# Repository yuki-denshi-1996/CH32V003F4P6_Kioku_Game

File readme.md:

## 概要
CH32V003F4P6を用いた記憶ゲームです。  
オマケ機能として、1分刻みのタイマー機能も実装してあります。  

## 説明
赤ボタン(PD4)を押すと、ゲームスタートです。  
色と音がなりますので、順番を覚え、ボタンを押してください。  
間違えるとゲームオーバーとなります。  
この時、ハイスコアが更新された場合、ゲームスタート直後の数字のハイスコアが更新されます。  

黄色ボタン(PD7)を押しながら、赤ボタン(PD4)を押すと、ハイスコアがリセットされます。  
(この時、起動直後に7セグメントLEDにCと表示されます)  

黄色ボタン(PD7)を押しながら、青ボタン(PD6)を押すと、難易度の変更ができます。
1(簡単) ~ 9(難しい)まで調整できます。  

緑ボタン(PD5)を押すと、タイマーモードに移行します。  
タイマーモード中に赤ボタン(PD4)を押すことで、リセットされます。  
青ボタン(PD6)と黄色ボタン(PD7)で時間が設定できます。(1分~9分 1分刻み)    
時間を設定した後、緑ボタン(PD5)を押すと、タイマーがスタートします。  
タイマー終了後、緑ボタン(PD5)を押すと、音が停止します。  

## プログラムについて
MounRiver Studio V1.9.1で作成しています。  
User/Kioku_game_program.hに様々な宣言がされています。  
音の周波数などの定数を編集することなどが可能です。  

## 注意点
CH32V003F4P6のNRSTピンをIOピンとして使用してください。  
変更はWCH-LinkUtilityを使うと簡単です。  

## 回路図
回路図はCircuitフォルダにKiCad形式と画像形式で配布しています。  
ご活用ください。  
(基本的に回路図を変更しなければ、配布したプログラムを入れれば動作します)  

部品表は、PDF形式にて配布しています。  
基本的に、秋月電子通商様で手に入る部品を使用しています。

## 問題点について
簡単に自作したプログラムのため、プログラムが汚いです。ご了承ください。  
また、バグ等の問題があった場合、Issuesにお書きください。時間があるときに、修正します。  

## 再配布や使用について
バグ等、修正などができませんので、プログラムソースの再配布はお控えください。  

特にライセンス等を指定していませんが、自由に使用していただいて構いません。  
文化祭等での配布や、キット販売なども構いません。自由にお使いください。  
ただし、プログラムや回路図の使用に関しては、自己責任でお願い致します。  

不明点等有りましたら、下の連絡先までご連絡ください。(できるだけ早く返信します)  

## 連絡先
メールアドレス：matsukawa.software@gmail.com

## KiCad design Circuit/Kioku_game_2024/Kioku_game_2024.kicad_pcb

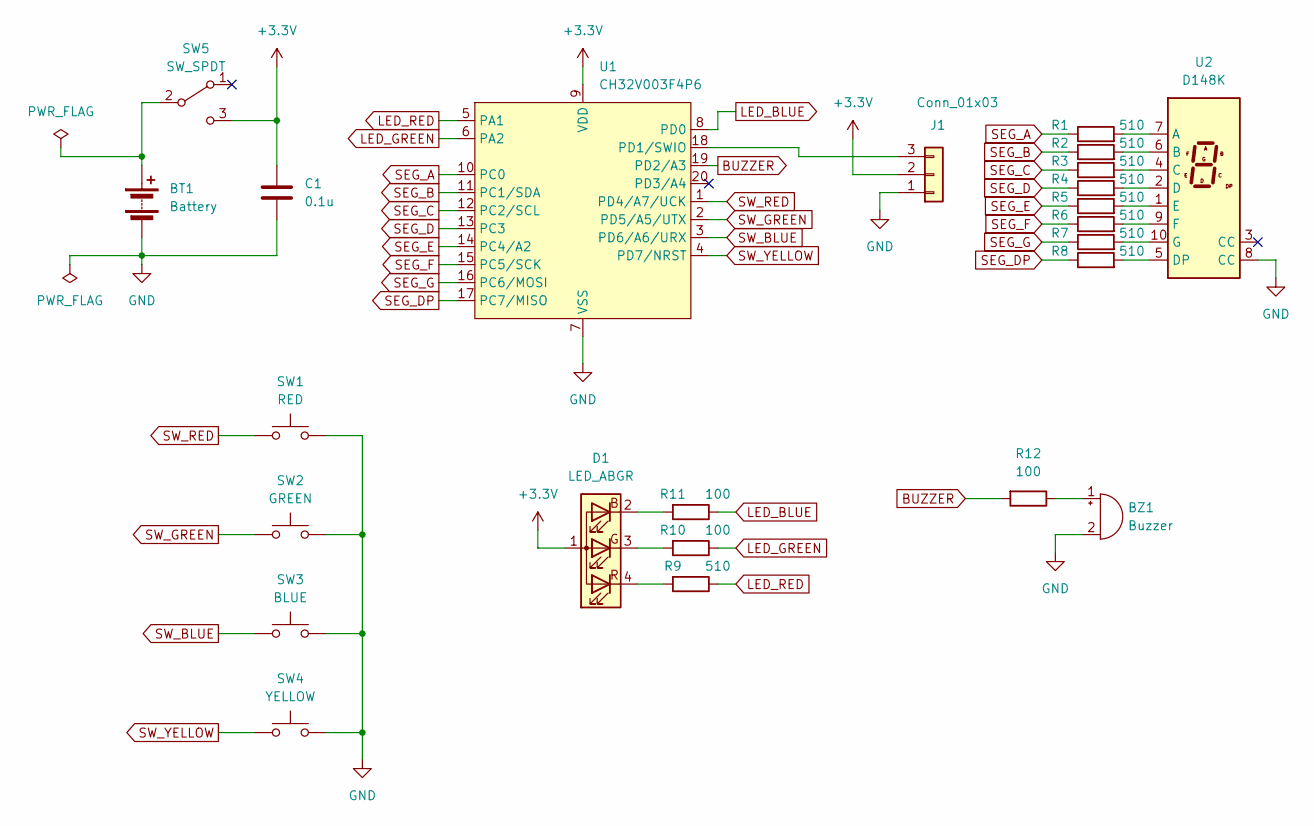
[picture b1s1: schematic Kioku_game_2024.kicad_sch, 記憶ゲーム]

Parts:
BT1: Battery; Coin_Cell_Batt_CR2032
BZ1: Buzzer; AKI_CERAMIC_BUZZER_PKM13EPYH4000-A0
C1: 0.1u; C_DISK_P5.0mm
D1: LED_ABGR; LED_BL-FL7680RGB
J1: Conn_01x03; PinSocket_1x03_P2.54mm_Vertical
R1, R2, R3, R4, R5, R6, R7, R8, R9: 510; R_1_4W
R10, R11, R12: 100; R_1_4W
SW1: RED; SW_PUSH_6mm
SW2: GREEN; SW_PUSH_6mm
SW3: BLUE; SW_PUSH_6mm
SW4: YELLOW; SW_PUSH_6mm
SW5: SW_SPDT; Yuki_PinHeader_1x03_P2.54mm_Vertical
U1: CH32V003F4P6; TSSOP-20_4.4x6.5mm_P0.65mm
U2: D148K; 7SegmentLED_LTS6760_LTS6780

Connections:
+3.3V: C1.1, D1.1 (A), J1.2, SW5.3 (C), U1.9 (VDD)
BUZZER: R12.2, U1.19 (PD2/A3)
GND: BT1.2 (-), BZ1.2 (+), C1.2, J1.1, SW1.2, SW2.2, SW3.2, SW4.2, U1.7 (VSS), U2.8 (CC)
LED_BLUE: R11.1, U1.8 (PD0)
LED_GREEN: R10.1, U1.6 (PA2)
LED_RED: R9.1, U1.5 (PA1)
unnamed: BT1.1 (+), SW5.2 (B)
unnamed: BZ1.1 (-), R12.1
unnamed: D1.2 (BK), R11.2
unnamed: D1.3 (GK), R10.2
unnamed: D1.4 (RK), R9.2
unnamed: J1.3, U1.18 (PD1/SWIO)
unnamed: R1.2, U2.7 (A)
unnamed: R2.2, U2.6 (B)
unnamed: R3.2, U2.4 (C)
unnamed: R4.2, U2.2 (D)
unnamed: R8.2, U2.5 (DP)
unnamed: R5.2, U2.1 (E)
unnamed: R6.2, U2.9 (F)
unnamed: R7.2, U2.10 (G)
SEG_A: R1.1, U1.10 (PC0)
SEG_B: R2.1, U1.11 (PC1/SDA)
SEG_C: R3.1, U1.12 (PC2/SCL)
SEG_D: R4.1, U1.13 (PC3)
SEG_DP: R8.1, U1.17 (PC7/MISO)
SEG_E: R5.1, U1.14 (PC4/A2)
SEG_F: R6.1, U1.15 (PC5/SCK)
SEG_G: R7.1, U1.16 (PC6/MOSI)
SW_BLUE: SW3.1, U1.3 (PD6/A6/URX)
SW_GREEN: SW2.1, U1.2 (PD5/A5/UTX)
SW_RED: SW1.1, U1.1 (PD4/A7/UCK)
SW_YELLOW: SW4.1, U1.4 (PD7/NRST)

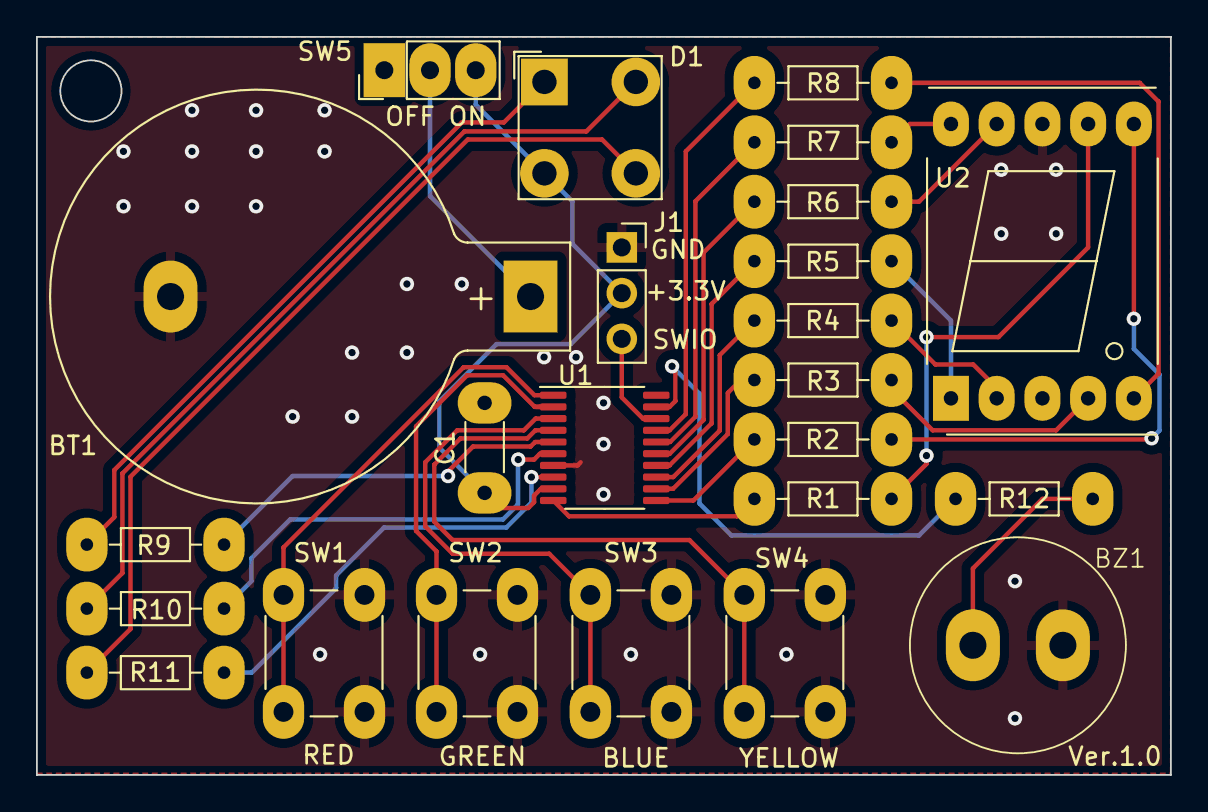
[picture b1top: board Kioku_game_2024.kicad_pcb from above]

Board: 2 copper layers, 63.0 x 41.0 mm, 24 parts (0 on the bottom side), 32 nets.

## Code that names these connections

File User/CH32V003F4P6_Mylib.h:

/*
 * CH32V003F4P6_Mylib.h
 *
 *  Created on: Jan 21, 2024
 *      Author: Yuki(denshi-1996)
 */

#ifndef USER_CH32V003F4P6_MYLIB_H_
#define USER_CH32V003F4P6_MYLIB_H_

//入出力関係_定義
#define MODE_OUTPUT 0b11 //50MHz スピード OUTPUT
#define MODE_OUTPUT_2MHz 0b10
#define MODE_OUTPUT_10MHz 0b01
#define MODE_INPUT 0b00
#define CNF_INPUT_ANALOG 0b00
#define CNF_INPUT_FLOAT 0b01
#define CNF_INPUT_PULL 0b10
#define CNF_OUTPUT_PUSH_PULL 0b00
#define CNF_OUTPUT_OPEN_DRAIN 0b01
#define CNF_OUTPUT_FUNC_PUSH_PULL 0b10
#define CNF_OUTPUT_FUNC_OPEN_DRAIN 0b11

//ピン_定義
#define PA1 1
#define PA2 2
#define PC0 0
#define PC1 1
#define PC2 2
#define PC3 3
#define PC4 4
#define PC5 5
#define PC6 6
#define PC7 7
#define PD0 0
#define PD1 1
#define PD2 2
#define PD3 3
#define PD4 4
#define PD5 5
#define PD6 6
#define PD7 7


#define RA3 440
#define SI3 494
#define DO4 523
#define DO4S 554
#define RE4 587
#define MI4 659
#define FA4 698
#define SO4 794
#define RA4 440 * 2
#define SI4 494 * 2
#define DO5 523 * 2
#define RE5 587 * 2
#define MI5 659 * 2
#define FA5 698 * 2
#define SO5 794 * 2

//ユーザーオプション設定
int PD7_IO_Mode(void); //PD7を標準で使用
int PD7_NRST_Mode(void); //PD7をNRST(12ms typ)で使用

//クロック設定
void Clock_init_PLL(void);
void Clock_init_8MHz(void);

//入出力設定
void pin_init(void);

//Timer2 割り込み設定
void TIM2_interrupt_init(void);

//Timer1 PWM初期化設定
void TIM1_PWM_init(void);
//TIM1_PWMを用いたtone関数 (TIM1_CH1 PD2)
void tone(int freq);
//toneを止める関数
void no_tone(void);

//FLASH書き込み関数
void FLASH_write(uint32_t Address, uint16_t Data);
//FLASH読み出し関数
uint16_t FLASH_read(uint32_t Address);
//FLASH削除関数
void FLASH_Erase(volatile uint32_t Address);


//特定ビット置き換え関数(レジスタ操作特化)
uint32_t bit_replace(uint32_t data, uint32_t byte, uint8_t len, uint8_t shift);

#endif /* USER_CH32V003F4P6_MYLIB_H_ */

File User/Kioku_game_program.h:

/*
 * Kioku_test_program.h
 *
 *  Created on: Jan 23, 2024
 *      Author: yuki(denshi-1996)
 */
#include "CH32V003F4P6_Mylib.h"

#ifndef USER_KIOKU_GAME_PROGRAM_H_
#define USER_KIOKU_GAME_PROGRAM_H_

#define LED_RED PD0
#define LED_GREEN PA2
#define LED_BLUE PA1

#define RED 1
#define GREEN 2
#define BLUE 3
#define YELLOW 4

#define SW_RED PD4
#define SW_GREEN PD5
#define SW_BLUE PD6
#define SW_YELLOW PD7

#define SEG_DOT 0x80

#define MODE_START 0
#define MODE_GAME_START 5
#define MODE_RANDOM 10
#define MODE_LED_BEEP 17
#define MODE_WAIT 15
#define MODE_JUDGE 20
#define MODE_CLEAR_ONCE 25
#define MODE_CLEAR 30
#define MODE_GAMEOVER 100
#define MODE_GAMEOVER_RUN 110
#define MODE_TIMER_SELECT 500
#define MODE_TIMER_SECTION 530
#define MODE_TIMER_END 550

#define HISCORE_FLASH 0x08003FC0
#define DIF_TIME_FLASH 0x08003FC2

#define SEG_SEQUENCE_WAIT_TIME 600
#define SEG_SEQUENCE_1DEG_WAIT_TIME 400

//#define RED_BEEP SI4
//#define GREEN_BEEP SO4
//#define BLUE_BEEP RA4
//#define YELLOW_BEEP RE4
#define RED_BEEP DO4
#define GREEN_BEEP RE4
#define BLUE_BEEP MI4
#define YELLOW_BEEP FA4
//#define RED_BEEP DO4
//#define GREEN_BEEP DO4
//#define BLUE_BEEP DO4
//#define YELLOW_BEEP DO4

#define GAMEOVER_BEEP1 DO4S
#define GAMEOVER_BEEP2 DO4S

#define TIMER_BEEP 4000

//7セグに数字を出力する用途で使用
void segment_out(int num);
//7セグに文字を出力する用途で使用
void segment_out_char(char moji);
#endif /* USER_KIOKU_GAME_PROGRAM_H_ */

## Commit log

2024-02-14 [add] ファーストコミット
    ファーストコミット
2024-02-15 [Update] 微小な修正
2024-02-15 [Add] 回路データの追加
    回路図と基板例・部品表を追加
2024-02-16 [Update] readme.mdの編集
    readme.mdの微小な編集
